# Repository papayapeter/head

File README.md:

# head
a head that moves it's face and breathes

documentation: [https://zenogries.com/portfolio/iamnotyourtool/](https://zenogries.com/portfolio/iamnotyourtool/)

## software
* arduino code that moves the motors and plays the sounds
* arduino code to find the minimum and maximum positions of the motors
* processing code to convert after effects tracking (of jaw and eyebrows) keyframes to an c++ array (AnimationData.h) so kind of a poor persons motion capture

## libraries
* [AccelStepper](http://www.airspayce.com/mikem/arduino/AccelStepper/) by Mike McCauley

## hardware
* [teensy 3.2](https://www.pjrc.com/teensy/teensyLC.html)
* [teensy audio adapter](https://www.pjrc.com/store/teensy3_audio.html)
* [a4988 stepper driver](https://www.pololu.com/product/1182)
* [nema 17 stepper](https://www.ebay.de/itm/Nema-17-Stepper-Motor-Schrittmotor-26Ncm-12V-0-4A-4-wire-1m-cable-3D-Printer/392163408983?hash=item5b4ec2bc57:g:sAsAAOSwfB9b2Q9~)
* carrier "sceleton" designed by me
* custom circuit boards

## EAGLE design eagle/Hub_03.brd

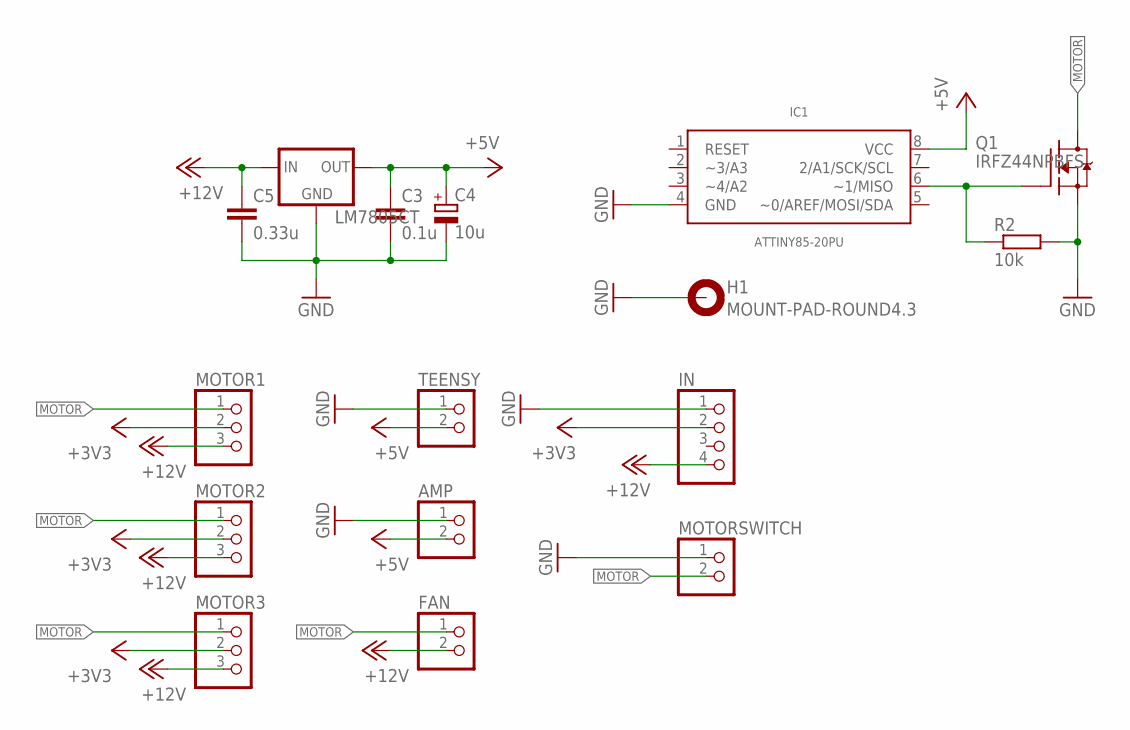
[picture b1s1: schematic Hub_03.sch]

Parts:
AMP: PINHD-1X2; 1X02
C3: 0.1u; C025-024X044
C4: 10u; E2,5-6E
C5: 0.33u; C025-024X044
FAN: PINHD-1X2; 1X02
H1: MOUNT-PAD-ROUND4.3; 4,3-PAD
IC1: ATTINY85-20PU; DIP08
IN: PINHD-1X4; 1X04
LM7805CT: 78XXS
MOTOR1, MOTOR2, MOTOR3: PINHD-1X3; 1X03
MOTORSWITCH: PINHD-1X2; 1X02
Q1: IRFZ44NPBFS; TO220-3S
R2: 10k; 0204/7
TEENSY: PINHD-1X2; 1X02

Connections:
+3V3: IN.2, MOTOR1.2, MOTOR2.2, MOTOR3.2
+5V: AMP.2, C3.1, C4.+, IC1.8 (VCC), LM7805CT.OUT, TEENSY.2
+12V: C5.1, FAN.2, IN.4, LM7805CT.IN, MOTOR1.3, MOTOR2.3, MOTOR3.3
GND: AMP.1, C3.2, C4.-, C5.2, H1.B4,3, IC1.4 (GND), IN.1, LM7805CT.GND, MOTORSWITCH.1, Q1.S, R2.2, TEENSY.1
MOTOR: FAN.1, MOTOR1.1, MOTOR2.1, MOTOR3.1, MOTORSWITCH.2, Q1.D
unnamed: IC1.6 (~1/MISO), Q1.G, R2.1

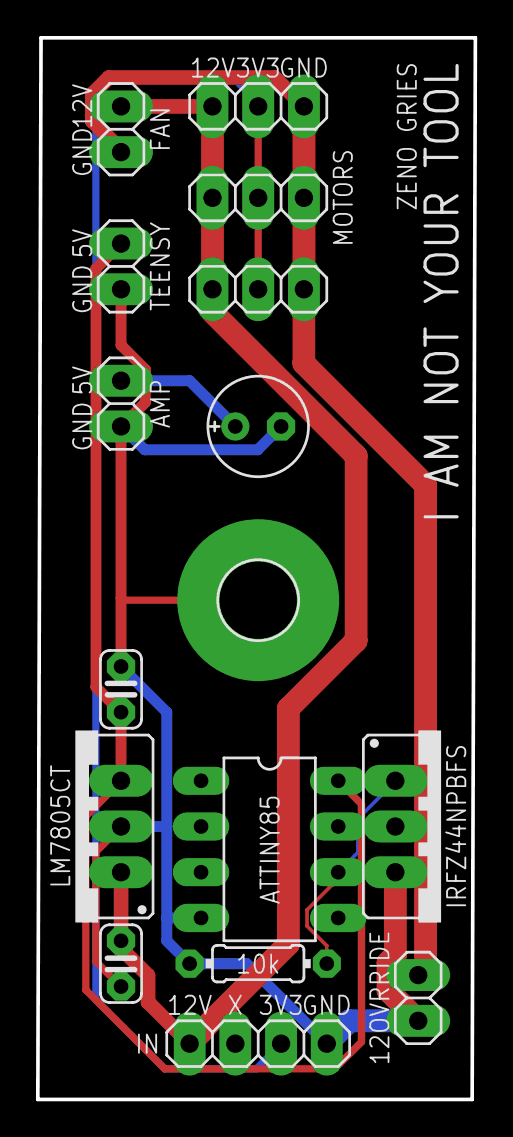
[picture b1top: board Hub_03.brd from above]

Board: 2 copper layers, 24.3 x 59.0 mm, 16 parts (0 on the bottom side), 6 nets.

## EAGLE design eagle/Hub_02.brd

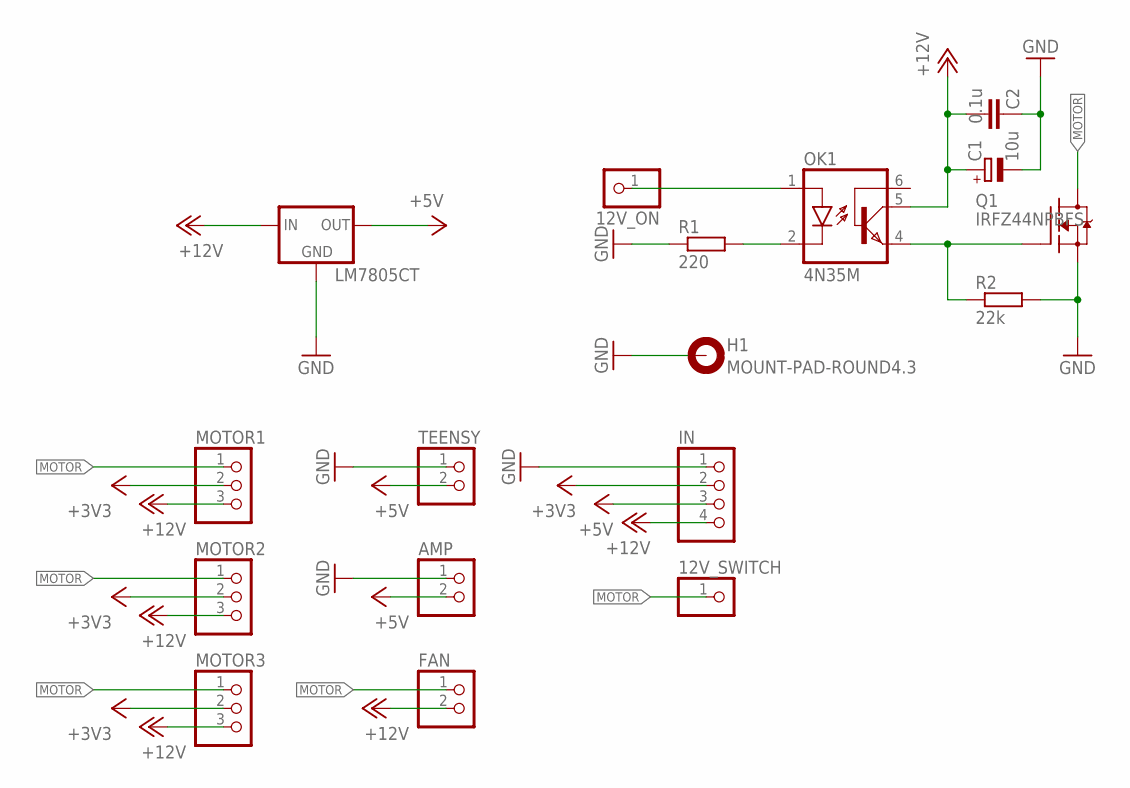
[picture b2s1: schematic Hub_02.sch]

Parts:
12V_ON, 12V_SWITCH: PINHD-1X1; 1X01
AMP: PINHD-1X2; 1X02
C1: 10u; E2,5-6E
C2: 0.1u; C025-024X044
FAN: PINHD-1X2; 1X02
H1: MOUNT-PAD-ROUND4.3; 4,3-PAD
IN: PINHD-1X4; 1X04
LM7805CT: 78XXS
MOTOR1, MOTOR2, MOTOR3: PINHD-1X3; 1X03
OK1: 4N35M; DIL06
Q1: IRFZ44NPBFS; TO220-3S
R1: 220; 0204/7
R2: 22k; 0204/7
TEENSY: PINHD-1X2; 1X02

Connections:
+3V3: IN.2, MOTOR1.2, MOTOR2.2, MOTOR3.2
+5V: AMP.2, IN.3, LM7805CT.OUT, TEENSY.2
+12V: C1.+, C2.2, FAN.2, IN.4, LM7805CT.IN, MOTOR1.3, MOTOR2.3, MOTOR3.3, OK1.5 (COL)
GND: AMP.1, C1.-, C2.1, H1.B4,3, IN.1, LM7805CT.GND, Q1.S, R1.1, R2.2, TEENSY.1
MOTOR: 12V_SWITCH.1, FAN.1, MOTOR1.1, MOTOR2.1, MOTOR3.1, Q1.D
unnamed: OK1.2 (C), R1.2
unnamed: OK1.4 (EMI), Q1.G, R2.1
unnamed: 12V_ON.1, OK1.1 (A)

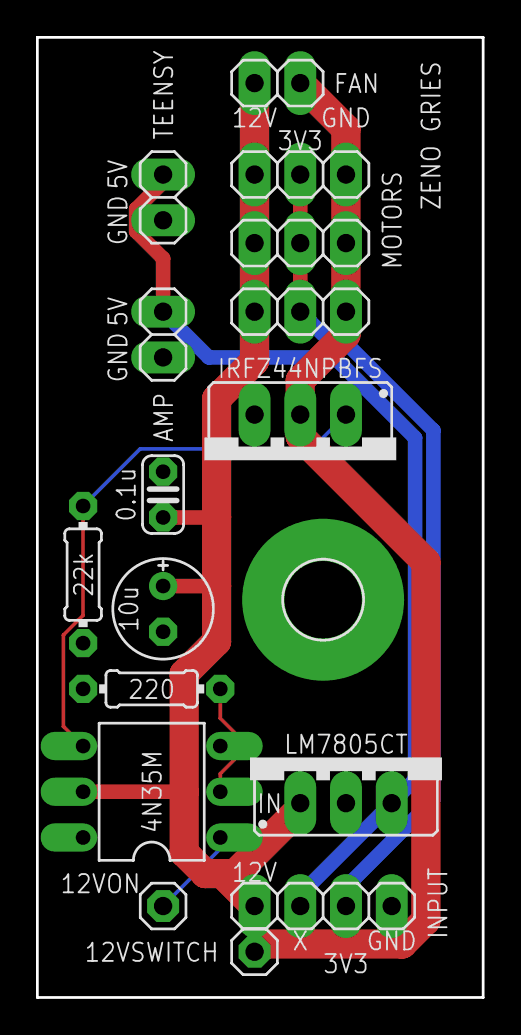
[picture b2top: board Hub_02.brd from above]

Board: 2 copper layers, 24.8 x 53.3 mm, 17 parts (0 on the bottom side), 8 nets.

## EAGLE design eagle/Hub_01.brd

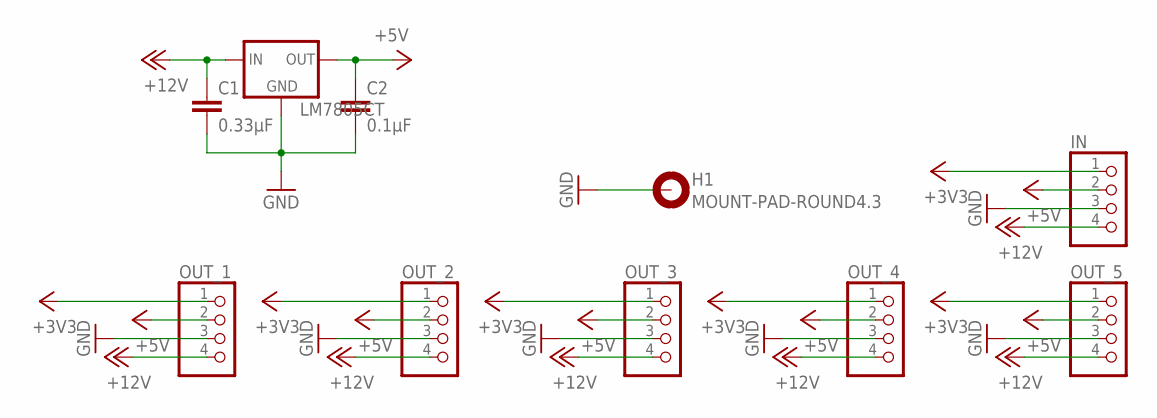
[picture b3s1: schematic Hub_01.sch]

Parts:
C1: 0.33µF; C025-024X044
C2: 0.1µF; C025-024X044
H1: MOUNT-PAD-ROUND4.3; 4,3-PAD
IN: PINHD-1X4; 1X04
LM7805CT: 78XXS
OUT_1, OUT_2, OUT_3, OUT_4, OUT_5: PINHD-1X4; 1X04

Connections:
+3V3: IN.1, OUT_1.1, OUT_2.1, OUT_3.1, OUT_4.1, OUT_5.1
+5V: C2.1, IN.2, LM7805CT.OUT, OUT_1.2, OUT_2.2, OUT_3.2, OUT_4.2, OUT_5.2
+12V: C1.1, IN.4, LM7805CT.IN, OUT_1.4, OUT_2.4, OUT_3.4, OUT_4.4, OUT_5.4
GND: C1.2, C2.2, H1.B4,3, IN.3, LM7805CT.GND, OUT_1.3, OUT_2.3, OUT_3.3, OUT_4.3, OUT_5.3

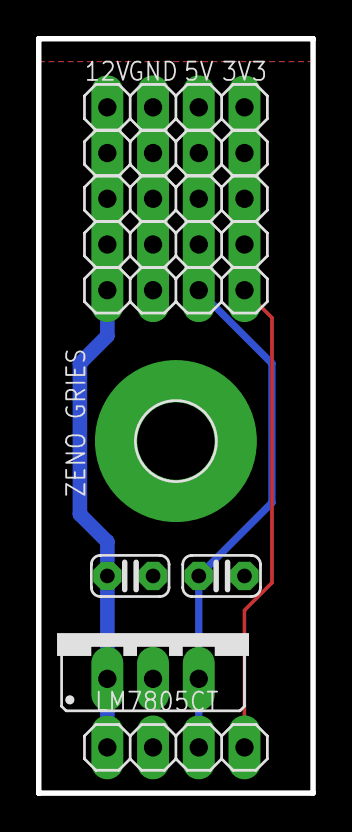
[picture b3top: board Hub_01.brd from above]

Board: 2 copper layers, 15.2 x 41.9 mm, 10 parts (0 on the bottom side), 4 nets.

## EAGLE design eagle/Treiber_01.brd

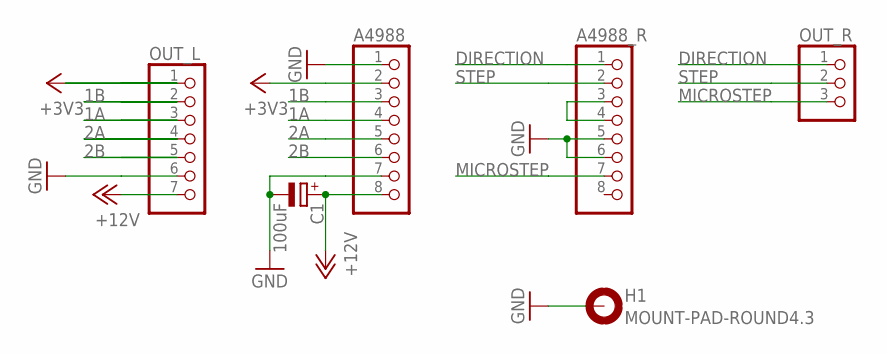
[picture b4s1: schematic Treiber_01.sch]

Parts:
A4988, A4988_R: PINHD-1X8; 1X08
C1: 100uF; E3,5-8
H1: MOUNT-PAD-ROUND4.3; 4,3-PAD
OUT_L: PINHD-1X7; 1X07
OUT_R: PINHD-1X3; 1X03

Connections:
1A: A4988.4, OUT_L.3
1B: A4988.3, OUT_L.2
2A: A4988.5, OUT_L.4
2B: A4988.6, OUT_L.5
+3V3: A4988.2, OUT_L.1
+12V: A4988.8, C1.+, OUT_L.7
DIRECTION: A4988_R.1, OUT_R.1
GND: A4988.1, A4988.7, A4988_R.5, A4988_R.6, C1.-, H1.B4,3, OUT_L.6
MICROSTEP: A4988_R.7, OUT_R.3
unnamed: A4988_R.3, A4988_R.4
STEP: A4988_R.2, OUT_R.2

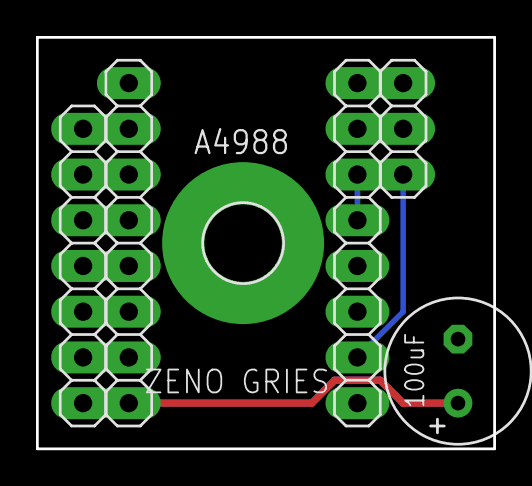
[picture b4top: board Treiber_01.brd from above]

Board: 2 copper layers, 25.4 x 22.9 mm, 6 parts (0 on the bottom side), 11 nets.

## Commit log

2019-06-14 correct error
2019-06-20 Create LICENSE
2020-04-11 corrected audio distortions
2020-04-11 corrected comments
2020-04-11 safety first
2020-04-13 added amp
2020-09-30 added new hub version
2020-10-03 added new hub with attiny
2020-10-04 added sound
2020-10-11 added new hub
2020-10-11 added headphone audio back in
2020-10-27 corrected timing & and wrong memory access
2020-11-03 changed volume
